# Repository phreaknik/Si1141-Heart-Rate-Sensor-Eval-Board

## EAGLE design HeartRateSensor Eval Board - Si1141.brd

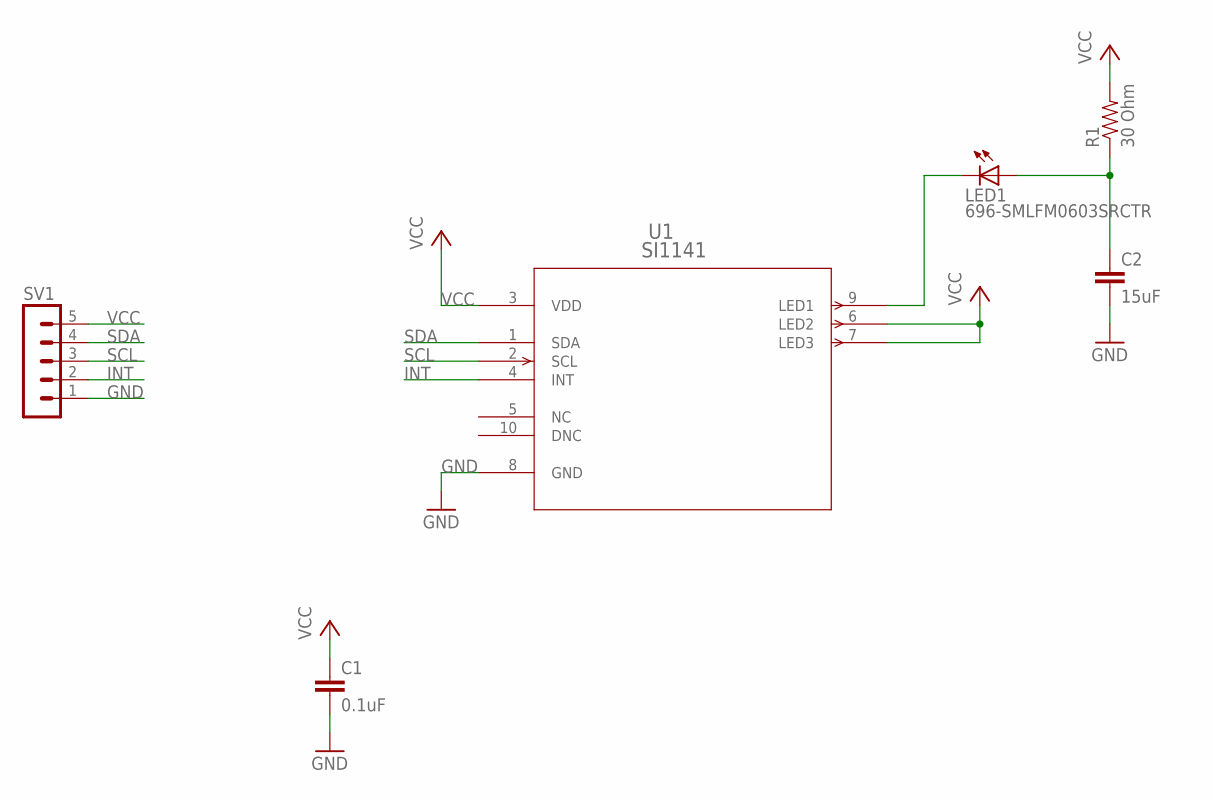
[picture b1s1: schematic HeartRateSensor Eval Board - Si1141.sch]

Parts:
C1: 0.1uF; 0603-CAP
C2: 15uF; 0603-CAP
LED1: 696-SMLFM0603SRCTR; CHIP-LED0603
R1: 30 Ohm; 0603
SV1: MA05-1
U1: SI1141; QFN10

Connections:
GND: C1.2, C2.2, SV1.1, U1.8 (GND)
INT: SV1.2, U1.4 (INT)
unnamed: LED1.C, U1.9 (LED1)
unnamed: C2.1, LED1.A, R1.1
SCL: SV1.3, U1.2 (SCL)
SDA: SV1.4, U1.1 (SDA)
VCC: C1.1, R1.2, SV1.5, U1.3 (VDD), U1.6 (LED2), U1.7 (LED3)

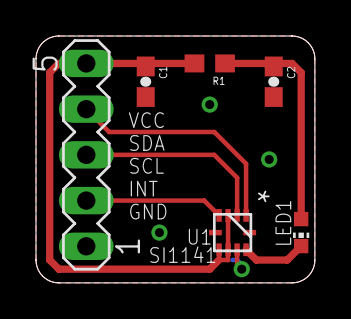
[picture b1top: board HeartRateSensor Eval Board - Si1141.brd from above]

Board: 2 copper layers, 15.5 x 13.7 mm, 6 parts (0 on the bottom side), 7 nets.

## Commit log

2015-12-08 :neckbeard: Added .gitattributes & .gitignore files

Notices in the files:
parts and their libraries:
SparkFun-Resistors: Licensing: Creative Commons ShareAlike 4.0 International - https://creativecommons.org/licenses/by-sa/4.0
